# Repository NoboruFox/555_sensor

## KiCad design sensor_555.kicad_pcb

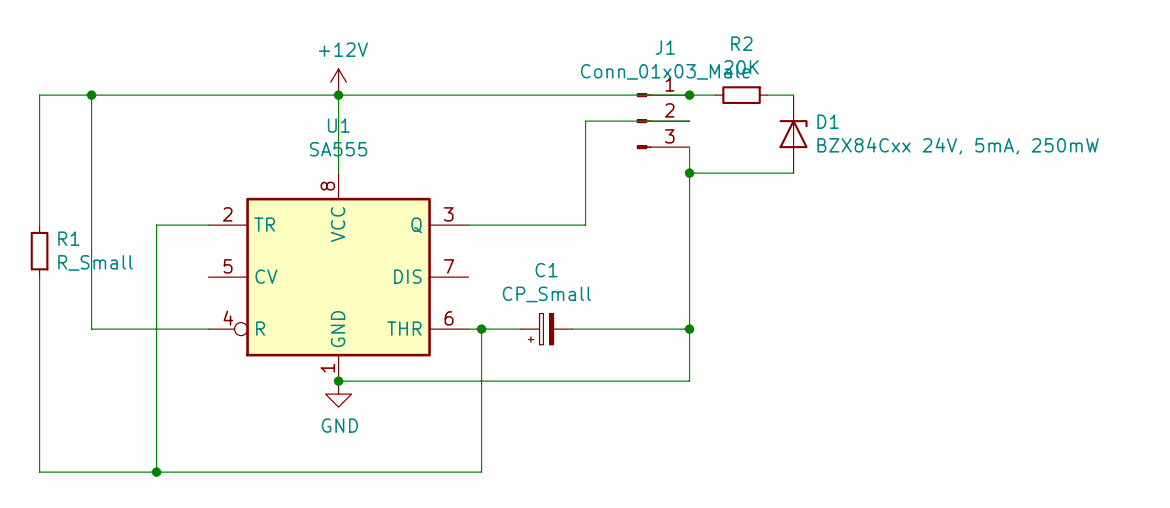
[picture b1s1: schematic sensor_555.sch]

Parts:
C1: CP_Small; CP_EIA-7343-31_Kemet-D
D1: BZX84Cxx 24V, 5mA, 250mW; D_SOT-23_ANK
J1: Conn_01x03_Male; PinHeader_1x03_P2.54mm_Horizontal
R1: R_Small; R_1206_3216Metric_Pad1.42x1.75mm_HandSolder
R2: 20K; R_1206_3216Metric_Pad1.42x1.75mm_HandSolder
U1: SA555; SOIC-8_3.9x4.9mm_P1.27mm

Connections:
+12V: J1.1, R1.2, R2.2, U1.4 (R), U1.8 (VCC)
GND: C1.2, D1.2 (A), J1.3, U1.1 (GND)
unnamed: C1.1, R1.1, U1.2 (TR), U1.6 (THR)
unnamed: D1.1 (K), R2.1
unnamed: J1.2, U1.3 (Q)

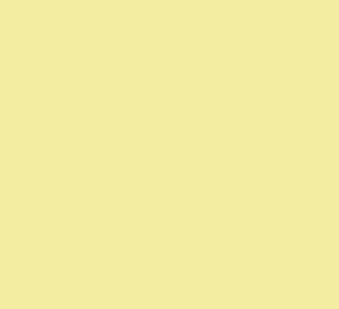
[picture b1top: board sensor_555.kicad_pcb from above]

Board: 2 copper layers, 6 parts (1 on the bottom side), 5 nets.

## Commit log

2019-10-31 555
    Ready project
2019-12-06 [FEAT]: sch is updated (values noted)
